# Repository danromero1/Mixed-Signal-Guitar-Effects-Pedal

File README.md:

# Mixed-Signal Guitar Effects Pedal

A standalone programmable guitar effects pedal implemented on a custom mixed-signal embedded platform with real-time DSP processing on an STM32 microcontroller.

---

## Overview

This project is the end-to-end design and bring-up of a custom 4-layer mixed-signal embedded platform for real-time audio acquisition, digital signal processing, and playback. An external high-resolution ADC and DAC interface with an STM32 microcontroller to enable deterministic, low-latency audio processing in a standalone system operating without a host PC.

The analog front end provides a high-impedance guitar input stage, precision biasing, and a 3rd-order Butterworth anti-aliasing filter to condition signals prior to conversion. Reconstruction filtering and low-noise output buffering suppress imaging artifacts and maintain low distortion across the audible band. PCB layout emphasizes controlled return paths, analog–digital domain isolation, low-impedance grounding, and consistent impedance to minimize coupling between sensitive analog circuitry and high-speed digital switching.

Power delivery is implemented using a USB-C input feeding a multi-rail regulation architecture to support low-noise analog supplies and regulated digital rails. All power stages and filter networks were simulated and validated in LTspice prior to layout. Decoupling and bypass networks were optimized per device requirements to ensure supply stability under dynamic load conditions.

Firmware is developed bare-metal in STM32CubeIDE using timer-triggered ADC sampling, DMA-based double buffering, and deterministic interrupt scheduling. Digital signal processing algorithms—including soft-clipping distortion, equalization, and filtering—are implemented in C using the CMSIS-DSP library on a Cortex-M4 FPU platform. The system targets a 48 kHz sample rate with sub-5 ms end-to-end latency to preserve instrument responsiveness.

The platform serves as a practical environment for developing embedded firmware architecture, hardware–software co-design techniques, signal integrity practices, and real-time performance analysis while producing a functional guitar effects processor from schematic to working prototype.

---

## Key Objectives

- Design and validate a professional-grade mixed-signal PCB for low-noise audio applications  
- Implement deterministic real-time audio processing on embedded hardware  
- Develop practical experience with ADC/DAC interfacing, buffering, and latency management  
- Integrate hardware bring-up, firmware development, and signal characterization into a complete system  

---

## Features

### Hardware
- STM32 microcontroller with floating-point acceleration  
- External high-resolution ADC and DAC for audio conversion  
- 4-layer PCB optimized for signal integrity and power integrity  
- 3rd-order Butterworth analog anti-aliasing filter  
- USB-C powered multi-rail regulation architecture  

### DSP
- Bare-metal real-time audio pipeline  
- DMA-based double buffering  
- Soft-clipping distortion processing  
- Digital equalization and filtering  
- Deterministic sampling and low-latency operation  

---

## Technical Stack

### Hardware
- STM32 Microcontroller (ARM Cortex-M4 with FPU)  
- External high-resolution ADC and DAC  
- 4-layer PCB with controlled impedance and solid reference planes  
- USB-C power delivery and multi-rail regulation  

### Software & Tools
- KiCad – Schematic capture and PCB layout  
- STM32CubeIDE – Bare-metal firmware development  
- CMSIS-DSP – Optimized DSP library  
- LTspice – Circuit simulation and filter verification  
- C/C++ – Embedded firmware implementation  

---

## Design Process

### Circuit Design & Simulation
Analog input and output stages were designed for guitar signal conditioning, biasing, and bandwidth control. A 3rd-order Butterworth anti-aliasing filter was simulated and verified in LTspice along with ADC/DAC interfacing and power regulation networks.

### PCB Layout (4-Layer Stack-Up)

- **Layer 1:** Top signal layer (components, sensitive analog routing, high-speed digital signals)  
- **Layer 2:** Solid ground plane for low-impedance return paths and noise control  
- **Layer 3:** Secondary reference plane for shielding and analog/digital isolation  
- **Layer 4:** Bottom signal layer for routing and power distribution  

**Design considerations include:**
- Analog and digital domain isolation  
- Controlled impedance routing for high-speed signals  
- Low-inductance return paths and continuous reference planes  
- Robust decoupling and power integrity practices  

### Firmware Architecture

Firmware configures ADC, DAC, timers, DMA, and interrupt scheduling to form a deterministic real-time audio pipeline. Audio samples are acquired using timer-triggered ADC conversions, buffered via DMA, processed in interrupt callbacks, and streamed to the DAC with minimal jitter and latency.

DSP algorithms are implemented in C using CMSIS-DSP primitives and floating-point arithmetic to accelerate development and maintain numerical stability.

---

## Development Status

### Completed
- Schematic design and circuit simulation  
- 3rd-order Butterworth filter design and verification  
- 4-layer PCB layout and stack-up definition  
- Component selection and BOM creation  

### In Progress
- Bare-metal firmware development  
- Real-time DSP implementation  
- PCB fabrication and assembly  

### Planned
- Hardware bring-up and validation  
- Audio performance measurement and characterization  
- Enclosure design and mechanical integration  
- Additional DSP effects (chorus, delay, reverb)  

---

## Technical Specifications

### Audio Path
- Input Impedance: 1 MΩ  
- Sample Rate: 48 kHz  
- Bit Depth: 16–24 bit (ADC dependent)  
- Frequency Response: 20 Hz – 20 kHz  
- Anti-Aliasing Filter: 3rd-order Butterworth, fc ≈ 20 kHz  

### Power
- Input: USB-C (5 V)  
- Internal Rails: 3.3 V (digital), ±5 V or +9 V (analog)  
- Estimated Current Consumption: 200–300 mA  

### Processing
- MCU: STM32 ARM Cortex-M4 with FPU  
- Target End-to-End Latency: < 5 ms  

---

## Engineering Focus

This project provides hands-on experience in:

- Mixed-signal PCB design and layout techniques  
- Real-time embedded firmware development  
- DMA-based buffering and interrupt-driven architectures  
- Analog signal conditioning and filter design  
- Audio signal processing fundamentals  
- Hardware bring-up and debugging on custom PCBs  
- Hardware–software co-design tradeoffs  

---

## Roadmap

### Phase 1 — Core Development (Current)
- Complete DSP firmware implementation  
- Fabricate and assemble PCB  
- Initial bring-up and debugging  

### Phase 2 — Refinement
- Audio performance characterization  
- Latency and CPU utilization optimization  
- PCB revision based on test results  

### Phase 3 — Enhancement
- Additional DSP effects  
- USB parameter control interface  
- Enclosure design and fabrication  

---

## References

### DSP
- *The Scientist and Engineer's Guide to Digital Signal Processing* — Steven W. Smith  
- *Understanding Digital Signal Processing* — Richard G. Lyons  
- *Small Signal Audio Design* — Douglas Self  

### Application Notes
- STM32 Audio Processing Application Notes  
- High-Speed PCB Design Guidelines  
- Audio ADC/DAC Interface Best Practices  

---

## License

This project is licensed under the MIT License. See the [LICENSE](LICENSE) file for details.

---

## Contact

**Daniel Romero**  
Email: daniel.romero@ieee.org  
Portfolio: https://electricalromero.com  
LinkedIn: https://www.linkedin.com/in/daniel-romero-ee/  

---

_Last updated: January 2026_

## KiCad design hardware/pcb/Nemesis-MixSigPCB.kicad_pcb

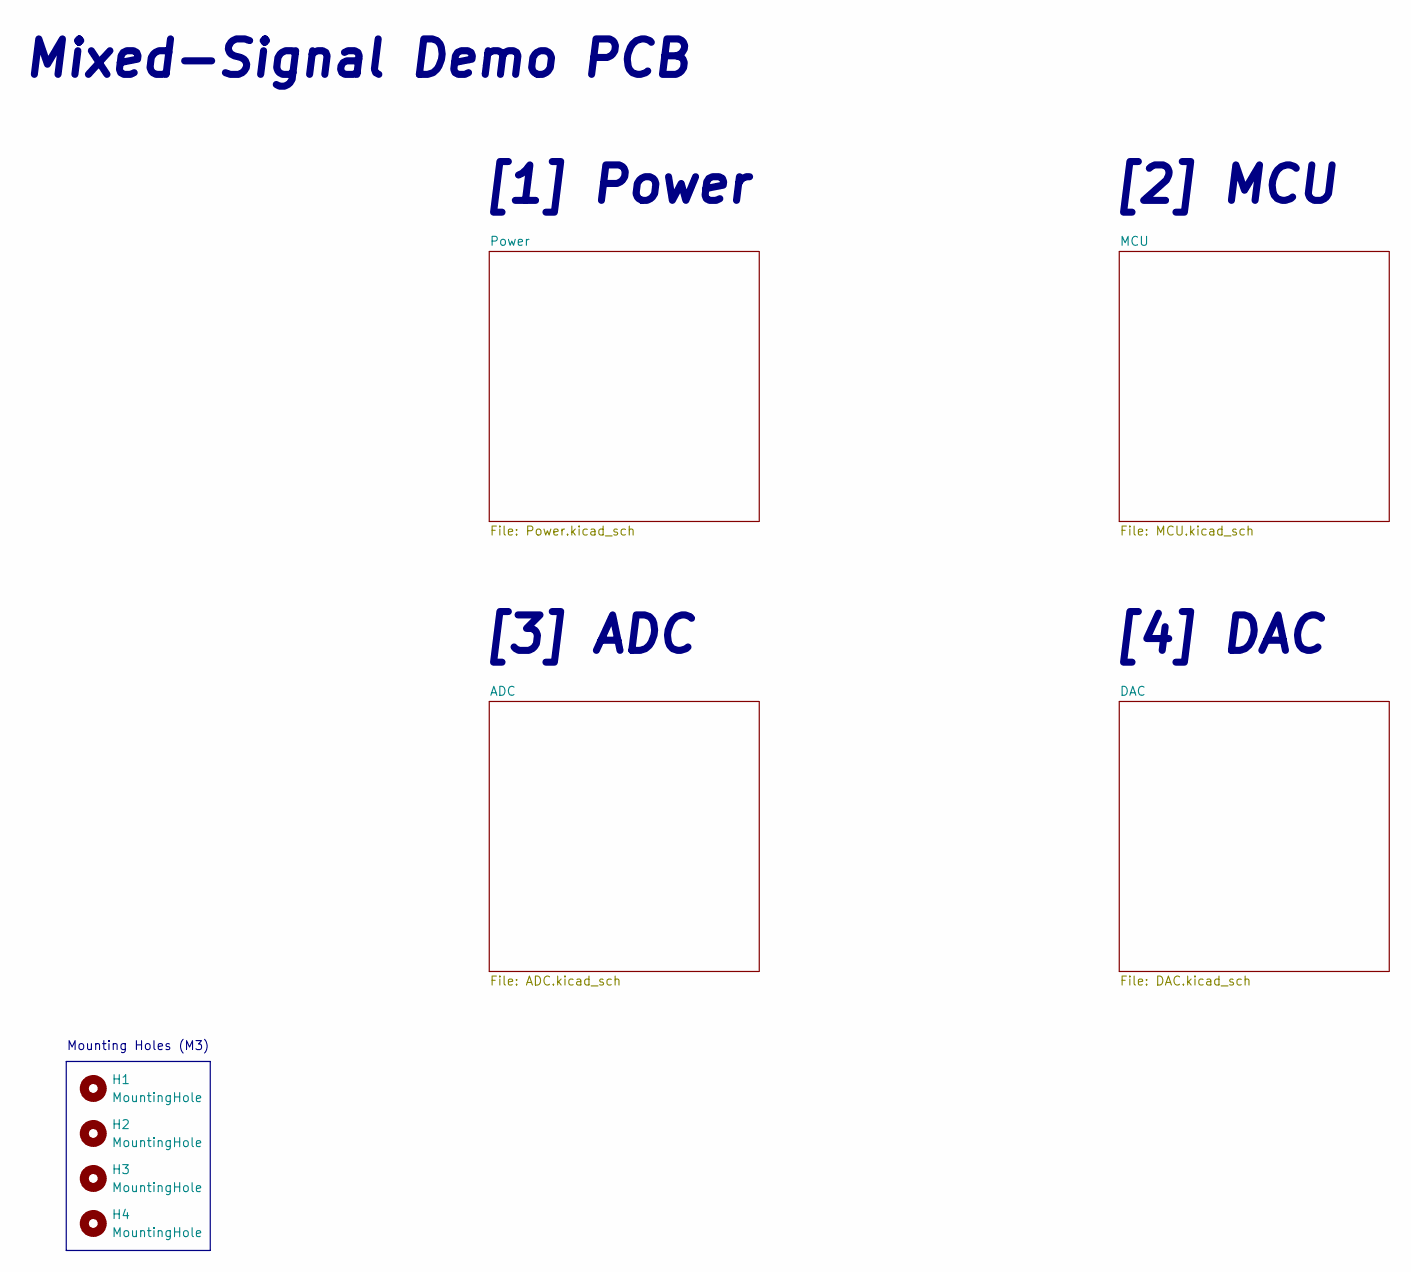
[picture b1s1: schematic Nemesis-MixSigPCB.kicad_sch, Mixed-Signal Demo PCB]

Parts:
H1, H2, H3, H4: MountingHole; MountingHole_3.2mm_M3

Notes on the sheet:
[4] DAC
Mixed-Signal Demo PCB
[3] ADC
Mounting Holes (M3)
[2] MCU
[1] Power

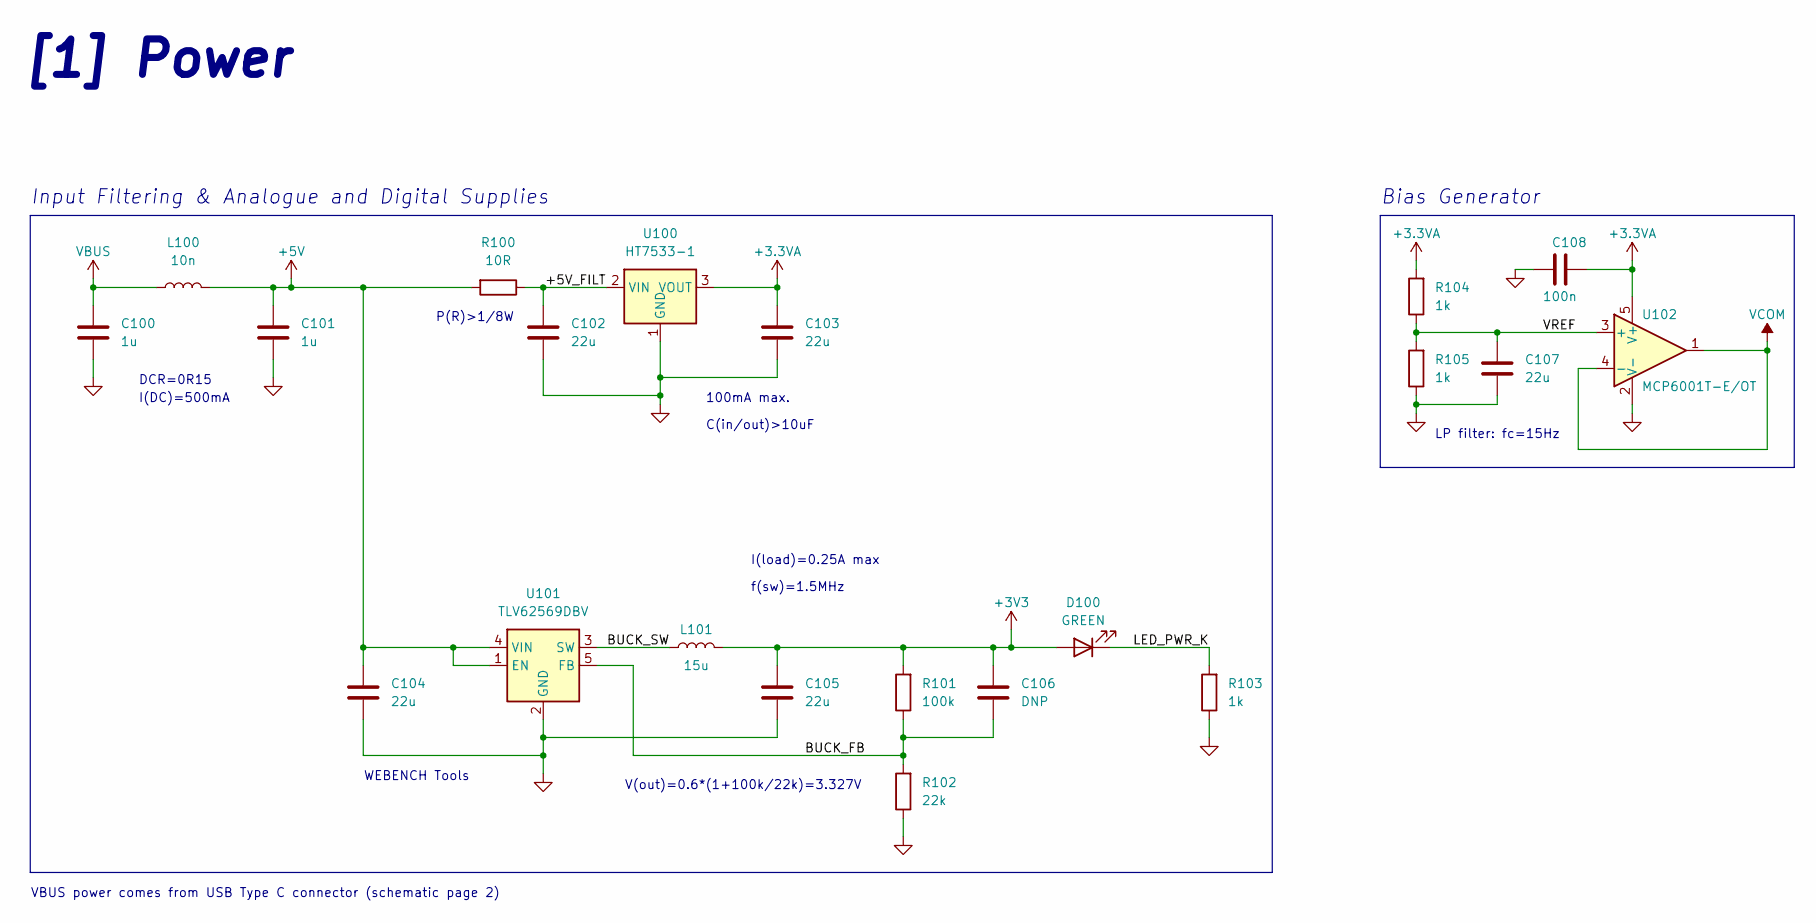
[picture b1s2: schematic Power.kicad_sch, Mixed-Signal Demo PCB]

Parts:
C100, C101: 1u; C_0603_1608Metric; Manufacturer Part Number CL10A105KB8NNNC
C102, C103, C104, C105, C107: 22u; C_0805_2012Metric; Manufacturer Part Number CL21A226MAQNNNE
C106: DNP; C_0402_1005Metric
C108: 100n; C_0402_1005Metric; Manufacturer Part Number CL05B104KO5NNNC
D100: GREEN; LED_0603_1608Metric; Manufacturer Part Number 19-217/GHC-YR1S2/3T
L100: 10n; L_0402_1005Metric; Manufacturer Part Number SDCL1005C10NJTDF
L101: 15u; L_Sunlord_MWSA0603S; Manufacturer Part Number MWSA0603S-150MT
R100: 10R; R_0805_2012Metric; Manufacturer Part Number 0805W8F100JT5E
R101: 100k; R_0402_1005Metric; Manufacturer Part Number 0402WGF1003TCE
R102: 22k; R_0402_1005Metric; Manufacturer Part Number 0402WGF2202TCE
R103, R104, R105: 1k; R_0402_1005Metric; Manufacturer Part Number 0402WGF1001TCE
U100: HT7533-1; SOT-89-3; Manufacturer Part Number HT7533-1
U101: TLV62569DBV; SOT-23-5; Manufacturer Part Number TLV62569DBVR
U102: MCP6001T-E/OT; SOT-23-5; Manufacturer Part Number MCP6001T-E/OT

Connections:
+3.3VA: C103.1, C108.1, R104.2, U100.3 (VOUT), U102.5 (V+); also elsewhere on the board
+3V3: C105.1, C106.1, D100.2 (A), L101.2, R101.2; also elsewhere on the board
+5V: C101.1, C104.1, L100.2, R100.2, U101.1 (EN), U101.4 (VIN); also elsewhere on the board
/Power/+5V_FILT: C102.1, R100.1, U100.2 (VIN)
/Power/BUCK_FB: C106.2, R101.1, R102.2, U101.5 (FB)
/Power/BUCK_SW: L101.1, U101.3 (SW)
/Power/LED_PWR_K: D100.1 (K), R103.2
/Power/VREF: C107.1, R104.1, R105.2, U102.3 (+)
GND: C100.2, C101.2, C102.2, C103.2, C104.2, C105.2, C107.2, C108.2, R102.1, R103.1, R105.1, U100.1 (GND), U101.2 (GND), U102.2 (V-); also elsewhere on the board
VBUS: C100.1, L100.1; also elsewhere on the board
VCOM: U102.1, U102.4 (-); also elsewhere on the board

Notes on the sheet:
DCR=0R15
C(in/out)>10uF
V(out)=0.6*(1+100k/22k)=3.327V
I(DC)=500mA
Bias Generator
LP filter: fc=15Hz
100mA max.
f(sw)=1.5MHz
VBUS power comes from USB Type C connector (schematic page 2)
P(R)>1/8W
I(load)=0.25A max
Input Filtering & Analogue and Digital Supplies
[1] Power
WEBENCH Tools

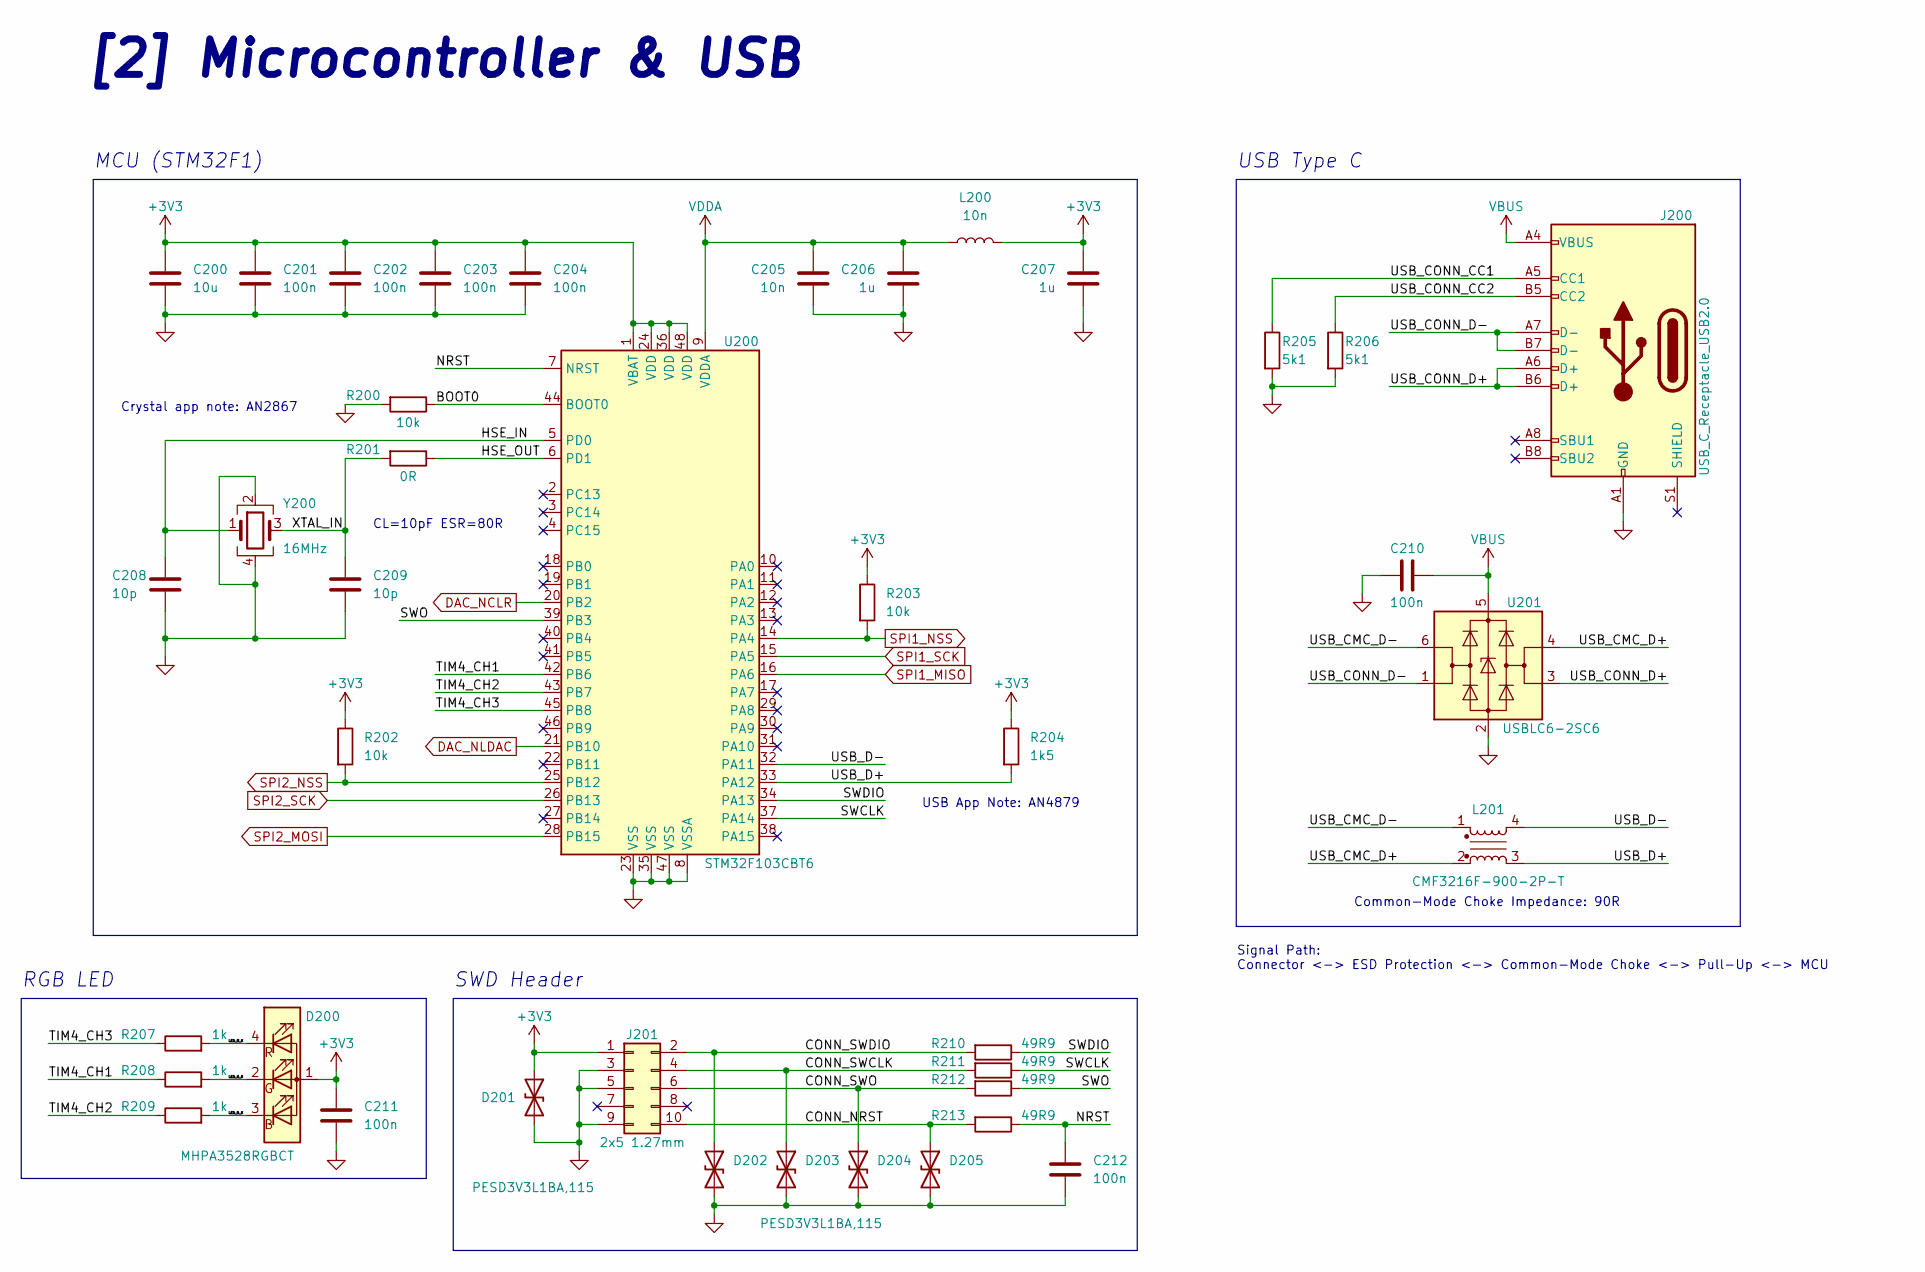
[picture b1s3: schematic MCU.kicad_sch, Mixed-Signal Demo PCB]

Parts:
C200: 10u; C_0603_1608Metric; Manufacturer Part Number CL10A106MA8NRNC
C201, C202, C203, C204, C210, C211, C212: 100n; C_0402_1005Metric; Manufacturer Part Number CL05B104KO5NNNC
C205: 10n; C_0402_1005Metric; Manufacturer Part Number CL05B103KB5NNNC
C206, C207: 1u; C_0603_1608Metric; Manufacturer Part Number CL10A105KB8NNNC
C208, C209: 10p; C_0402_1005Metric; Manufacturer Part Number CL05C100JB5NNNC
D200: MHPA3528RGBCT; Manufacturer Part Number MHPA3528RGBCT
D201, D202, D203, D204, D205: PESD3V3L1BA,115; D_SOD-323; Manufacturer Part Number PESD3V3L1BA,115
J200: USB_C_Receptacle_USB2.0; USB_C_Receptacle_HRO_TYPE-C-31-M-12; Manufacturer Part Number TYPE-C-31-M-12
J201: 2x5 1.27mm; PinHeader_2x05_P1.27mm_Vertical_SMD; Manufacturer Part Number FTSH-105-01-F-DV-K-TR
L200: 10n; L_0402_1005Metric; Manufacturer Part Number SDCL1005C10NJTDF
L201: CMF3216F-900-2P-T; L_CommonModeChoke_CMF3216F-900-2P-T; Manufacturer Part Number CMF3216F-900-2P-T
R200, R202, R203: 10k; R_0402_1005Metric; Manufacturer Part Number 0402WGF1002TCE
R201: 0R; R_0402_1005Metric; Manufacturer Part Number 0402WGF0000TCE
R204: 1k5; R_0402_1005Metric; Manufacturer Part Number 0402WGF1501TCE
R205, R206: 5k1; R_0402_1005Metric; Manufacturer Part Number 0402WGF5101TCE
R207, R208, R209: 1k; R_0402_1005Metric; Manufacturer Part Number 0402WGF1001TCE
R210, R211, R212, R213: 49R9; R_0402_1005Metric; Manufacturer Part Number 0402WGF499JTCE
U200: STM32F103CBT6; LQFP-48_7x7mm_P0.5mm; Manufacturer Part Number STM32F103CBT6
U201: USBLC6-2SC6; SOT-23-6; Manufacturer Part Number USBLC6-2SC6
Y200: 16MHz; Crystal_SMD_3225-4Pin_3.2x2.5mm; Manufacturer Part Number 7M16000017

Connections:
+3V3: C200.1, C201.1, C202.1, C203.1, C204.1, C207.1, C211.1, D200.1 (A), D201.1 (A1), J201.1 (Vcc), L200.2, R202.1, R203.1, R204.1, U200.1 (VBAT), U200.24 (VDD), U200.36 (VDD), U200.48 (VDD); also elsewhere on the board
/MCU/BOOT0: R200.1, U200.44 (BOOT0)
/MCU/CONN_NRST: D205.1 (A1), J201.10 (NRST), R213.2
/MCU/CONN_SWCLK: D203.1 (A1), J201.4 (SWDCLK), R211.2
/MCU/CONN_SWDIO: D202.1 (A1), J201.2 (SWDIO), R210.2
/MCU/CONN_SWO: D204.1 (A1), J201.6 (SWO), R212.2
/MCU/HSE_IN: C208.1, U200.5 (PD0), Y200.1
/MCU/HSE_OUT: R201.1, U200.6 (PD1)
/MCU/LED_B_K: D200.3 (BK), R209.2
/MCU/LED_G_K: D200.2 (GK), R208.2
/MCU/LED_R_K: D200.4 (RK), R207.2
/MCU/NRST: C212.1, R213.1, U200.7 (NRST)
/MCU/SWCLK: R211.1, U200.37 (PA14)
/MCU/SWDIO: R210.1, U200.34 (PA13)
/MCU/SWO: R212.1, U200.39 (PB3)
/MCU/TIM4_CH1: R208.1, U200.42 (PB6)
/MCU/TIM4_CH2: R209.1, U200.43 (PB7)
/MCU/TIM4_CH3: R207.1, U200.45 (PB8)
/MCU/USB_CMC_D+: L201.2, U201.4 (I/O2)
/MCU/USB_CMC_D-: L201.1, U201.6 (I/O1)
/MCU/USB_CONN_CC1: J200.A5 (CC1), R205.1
/MCU/USB_CONN_CC2: J200.B5 (CC2), R206.1
/MCU/USB_CONN_D+: J200.A6 (D+), J200.B6 (D+), U201.3 (I/O2)
/MCU/USB_CONN_D-: J200.A7 (D-), J200.B7 (D-), U201.1 (I/O1)
/MCU/USB_D+: L201.3, R204.2, U200.33 (PA12)
/MCU/USB_D-: L201.4, U200.32 (PA11)
/MCU/XTAL_IN: C209.1, R201.2, Y200.3
DAC_NCLR: U200.20 (PB2); also elsewhere on the board
DAC_NLDAC: U200.21 (PB10); also elsewhere on the board
GND: C200.2, C201.2, C202.2, C203.2, C204.2, C205.2, C206.2, C207.2, C208.2, C209.2, C210.2, C211.2, C212.2, D201.2 (A2), D202.2 (A2), D203.2 (A2), D204.2 (A2), D205.2 (A2), J200.A1 (GND), J200.A12 (GND), J200.B1 (GND), J200.B12 (GND), J201.3 (GND), J201.5 (GND), J201.9 (GNDDetect), R200.2, R205.2, R206.2, U200.8 (VSSA), U200.23 (VSS), U200.35 (VSS), U200.47 (VSS), U201.2 (GND), Y200.2, Y200.4; also elsewhere on the board
SPI1_MISO: U200.16 (PA6); also elsewhere on the board
SPI1_NSS: R203.2, U200.14 (PA4); also elsewhere on the board
SPI1_SCK: U200.15 (PA5); also elsewhere on the board
SPI2_MOSI: U200.28 (PB15); also elsewhere on the board
SPI2_NSS: R202.2, U200.25 (PB12); also elsewhere on the board
SPI2_SCK: U200.26 (PB13); also elsewhere on the board
VBUS: C210.1, J200.A4 (VBUS), J200.A9 (VBUS), J200.B4 (VBUS), J200.B9 (VBUS), U201.5 (VBUS); also elsewhere on the board
VDDA: C205.1, C206.1, L200.1, U200.9 (VDDA)

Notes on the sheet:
Signal Path: Connector <-> ESD Protection <-> Common-Mode Choke <-> Pull-Up <-> MCU
RGB LED
Crystal app note: AN2867
SWD Header
USB App Note: AN4879
Common-Mode Choke Impedance: 90R
[2] Microcontroller & USB
CL=10pF ESR=80R
MCU (STM32F1)
USB Type C

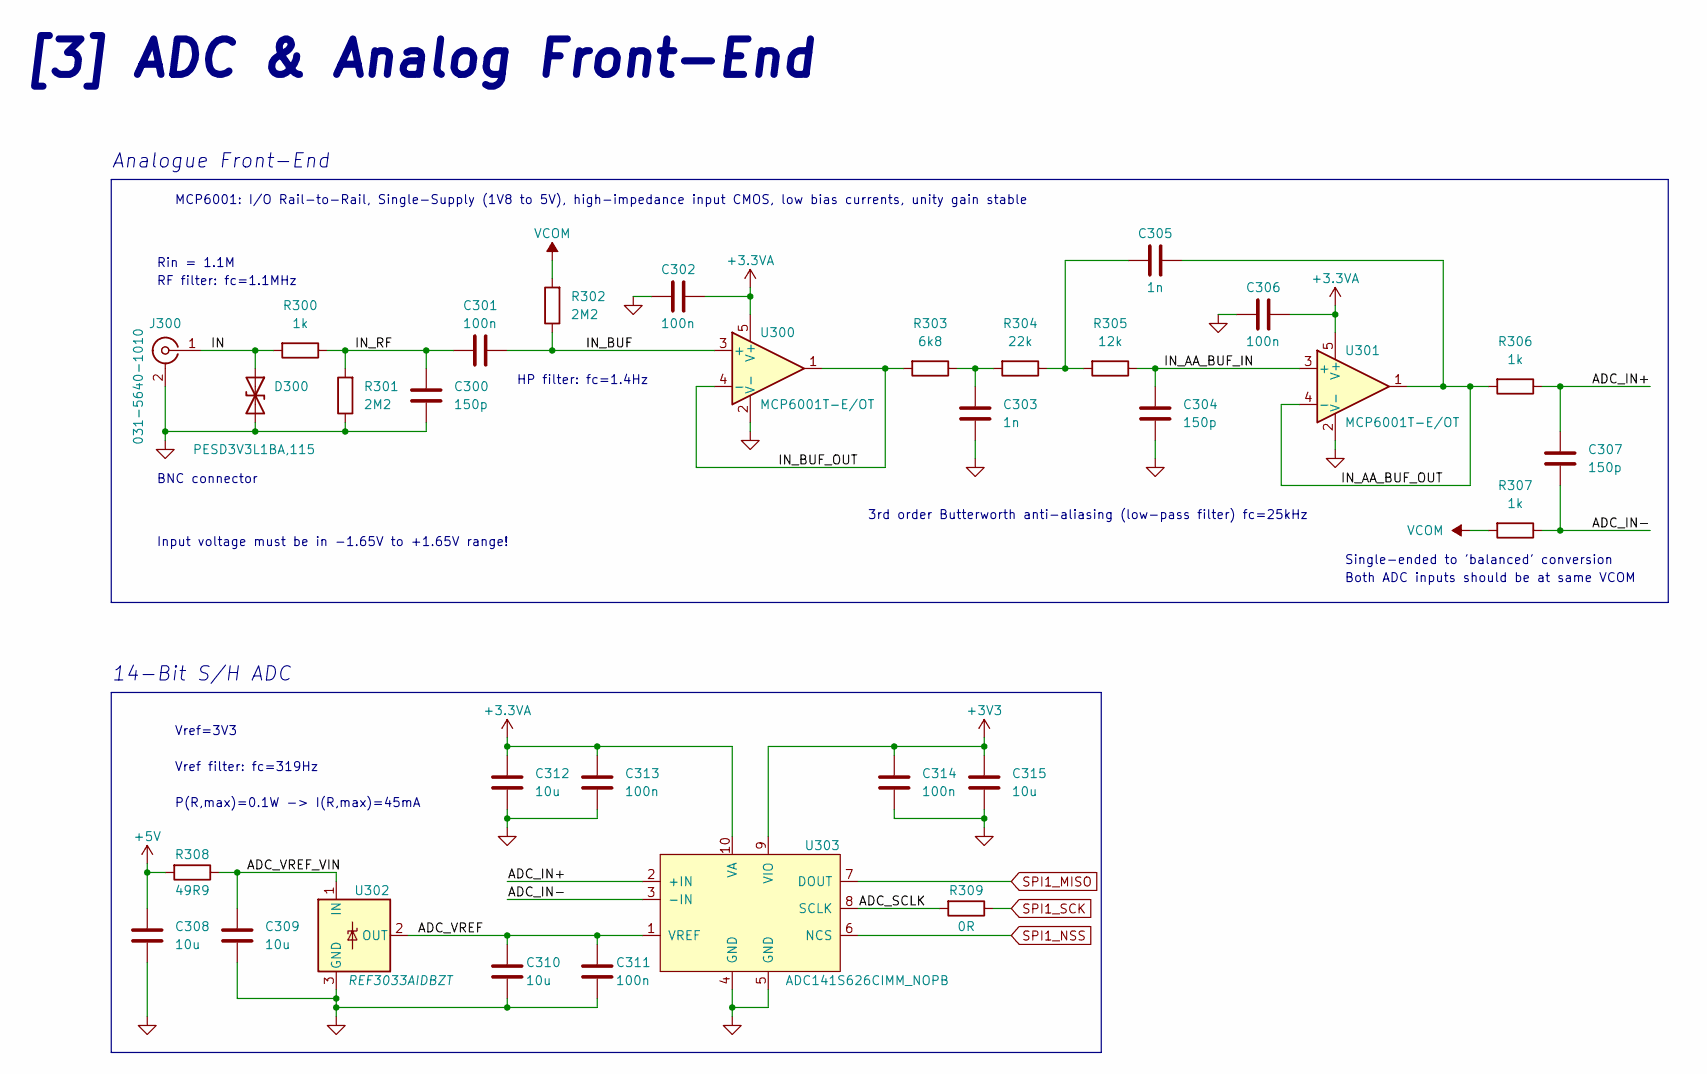
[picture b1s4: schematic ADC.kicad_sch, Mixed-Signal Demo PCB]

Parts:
C300, C304, C307: 150p; C_0402_1005Metric; Manufacturer Part Number CL05C151JB5NNNC
C301, C302, C306, C311, C313, C314: 100n; C_0402_1005Metric; Manufacturer Part Number CL05B104KO5NNNC
C303, C305: 1n; C_0402_1005Metric; Manufacturer Part Number 0402B102K500NT
C308, C309, C310, C312, C315: 10u; C_0603_1608Metric; Manufacturer Part Number CL10A106MA8NRNC
D300: PESD3V3L1BA,115; D_SOD-323; Manufacturer Part Number PESD3V3L1BA,115
J300: 031-5640-1010; AMPHENOL-BNC-031-5640-1010; Manufacturer Part Number 031-5640
R300, R306, R307: 1k; R_0402_1005Metric; Manufacturer Part Number 0402WGF1001TCE
R301, R302: 2M2; R_0402_1005Metric; Manufacturer Part Number 0402WGF2204TCE
R303: 6k8; R_0402_1005Metric; Manufacturer Part Number 0402WGF6801TCE
R304: 22k; R_0402_1005Metric; Manufacturer Part Number 0402WGF2202TCE
R305: 12k; R_0402_1005Metric; Manufacturer Part Number 0402WGF1202TCE
R308: 49R9; R_0402_1005Metric; Manufacturer Part Number 0402WGF499JTCE
R309: 0R; R_0402_1005Metric; Manufacturer Part Number 0402WGF0000TCE
U300, U301: MCP6001T-E/OT; SOT-23-5; Manufacturer Part Number MCP6001T-E/OT
U302: REF3033AIDBZT; SOT-23; Manufacturer Part Number REF3033AIDBZT
U303: ADC141S626CIMM_NOPB; VSSOP-10_3x3mm_P0.5mm; Manufacturer Part Number ADC141S626CIMM/NOPB

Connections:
+3.3VA: C302.1, C306.1, C312.1, C313.1, U300.5 (V+), U301.5 (V+), U303.10 (VA); also elsewhere on the board
+3V3: C314.1, C315.1, U303.9 (VIO); also elsewhere on the board
+5V: C308.1, R308.2; also elsewhere on the board
/ADC/ADC_IN+: C307.1, R306.1, U303.2 (+IN)
/ADC/ADC_IN-: C307.2, R307.1, U303.3 (-IN)
/ADC/ADC_SCLK: R309.2, U303.8 (SCLK)
/ADC/ADC_VREF: C310.1, C311.1, U302.2 (OUT), U303.1 (VREF)
/ADC/ADC_VREF_VIN: C309.1, R308.1, U302.1 (IN)
/ADC/IN: D300.1 (A1), J300.1 (In), R300.2
/ADC/IN_AA_BUF_IN: C304.1, R305.1, U301.3 (+)
/ADC/IN_AA_BUF_OUT: C305.2, R306.2, U301.1, U301.4 (-)
/ADC/IN_BUF: C301.1, R302.1, U300.3 (+)
/ADC/IN_BUF_OUT: R303.2, U300.1, U300.4 (-)
/ADC/IN_RF: C300.1, C301.2, R300.1, R301.2
GND: C300.2, C302.2, C303.2, C304.2, C306.2, C308.2, C309.2, C310.2, C311.2, C312.2, C313.2, C314.2, C315.2, D300.2 (A2), J300.2 (Ext), R301.1, U300.2 (V-), U301.2 (V-), U302.3 (GND), U303.4 (GND), U303.5 (GND); also elsewhere on the board
unnamed: C303.1, R303.1, R304.2
unnamed: C305.1, R304.1, R305.2
SPI1_MISO: U303.7 (DOUT); also elsewhere on the board
SPI1_NSS: U303.6 (NCS); also elsewhere on the board
SPI1_SCK: R309.1; also elsewhere on the board
VCOM: R302.2, R307.2; also elsewhere on the board

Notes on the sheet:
HP filter: fc=1.4Hz
Both ADC inputs should be at same VCOM
BNC connector
Rin = 1.1M
14-Bit S/H ADC
Vref filter: fc=319Hz
Input voltage must be in -1.65V to +1.65V range!
Analogue Front-End
Single-ended to 'balanced' conversion
RF filter: fc=1.1MHz
3rd order Butterworth anti-aliasing (low-pass filter) fc=25kHz
MCP6001: I/O Rail-to-Rail, Single-Supply (1V8 to 5V), high-impedance input CMOS, low bias currents, unity gain stable
P(R,max)=0.1W -> I(R,max)=45mA
Vref=3V3
[3] ADC & Analog Front-End

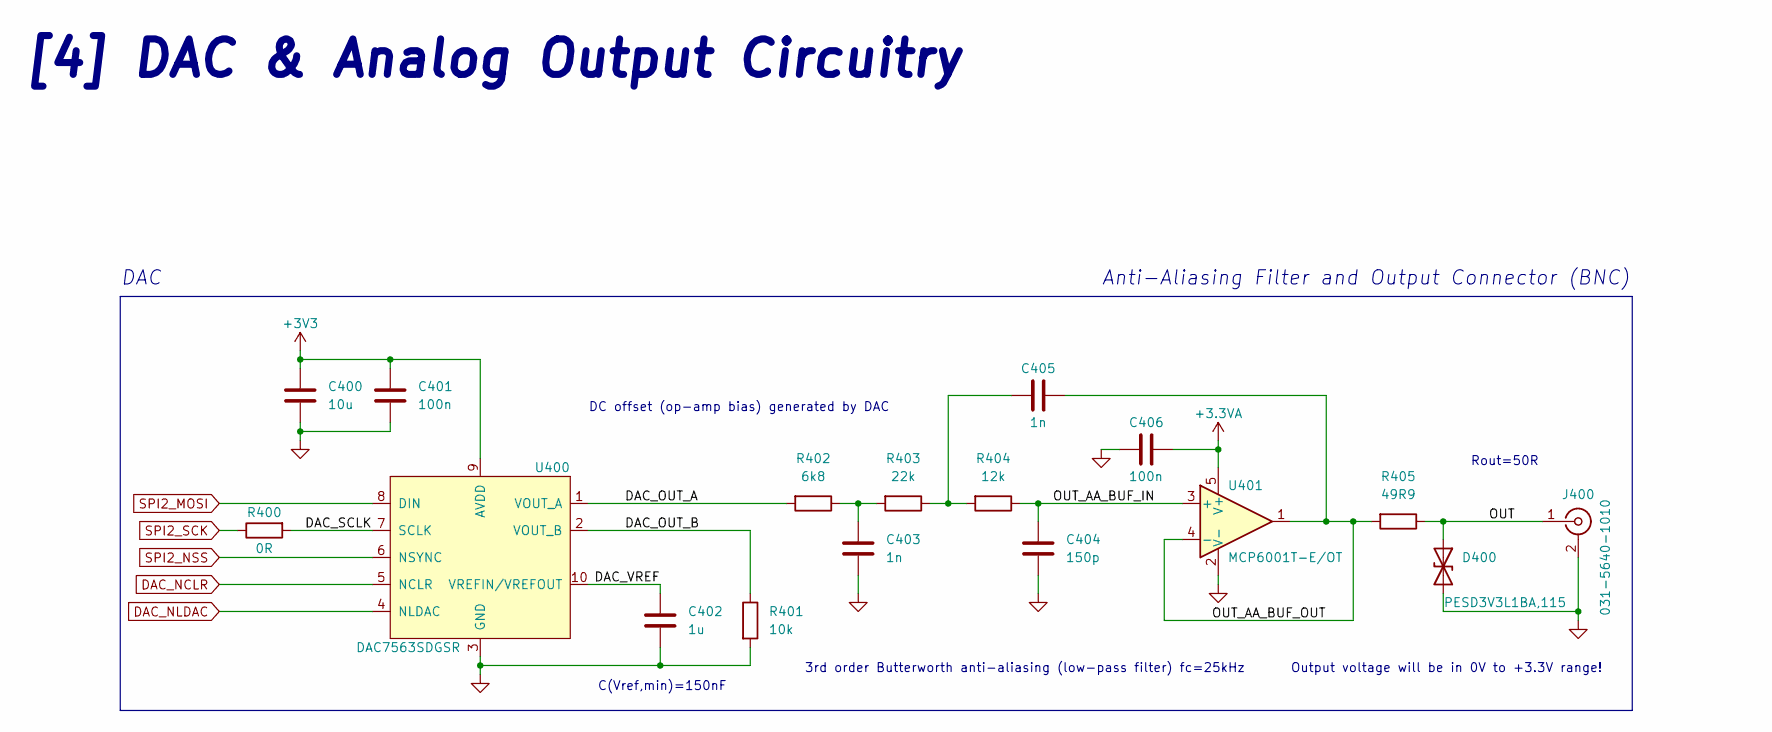
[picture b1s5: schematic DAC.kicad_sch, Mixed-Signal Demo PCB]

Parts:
C400: 10u; C_0603_1608Metric; Manufacturer Part Number CL10A106MA8NRNC
C401, C406: 100n; C_0402_1005Metric; Manufacturer Part Number CL05B104KO5NNNC
C402: 1u; C_0603_1608Metric; Manufacturer Part Number CL10A105KB8NNNC
C403, C405: 1n; C_0402_1005Metric; Manufacturer Part Number 0402B102K500NT
C404: 150p; C_0402_1005Metric; Manufacturer Part Number CL05C151JB5NNNC
D400: PESD3V3L1BA,115; D_SOD-323; Manufacturer Part Number PESD3V3L1BA,115
J400: 031-5640-1010; AMPHENOL-BNC-031-5640-1010; Manufacturer Part Number 031-5640
R400: 0R; R_0402_1005Metric; Manufacturer Part Number 0402WGF0000TCE
R401: 10k; R_0402_1005Metric; Manufacturer Part Number 0402WGF1002TCE
R402: 6k8; R_0402_1005Metric; Manufacturer Part Number 0402WGF6801TCE
R403: 22k; R_0402_1005Metric; Manufacturer Part Number 0402WGF2202TCE
R404: 12k; R_0402_1005Metric; Manufacturer Part Number 0402WGF1202TCE
R405: 49R9; R_0402_1005Metric; Manufacturer Part Number 0402WGF499JTCE
U400: DAC7563SDGSR; VSSOP-10_3x3mm_P0.5mm; Manufacturer Part Number DAC7563TDGSR
U401: MCP6001T-E/OT; SOT-23-5; Manufacturer Part Number MCP6001T-E/OT

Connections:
+3.3VA: C406.1, U401.5 (V+); also elsewhere on the board
+3V3: C400.1, C401.1, U400.9 (AVDD); also elsewhere on the board
/DAC/DAC_OUT_A: R402.2, U400.1 (VOUT_A)
/DAC/DAC_OUT_B: R401.1, U400.2 (VOUT_B)
/DAC/DAC_SCLK: R400.2, U400.7 (SCLK)
/DAC/DAC_VREF: C402.1, U400.10 (VREFIN/VREFOUT)
/DAC/OUT: D400.1 (A1), J400.1 (In), R405.1
/DAC/OUT_AA_BUF_IN: C404.1, R404.1, U401.3 (+)
/DAC/OUT_AA_BUF_OUT: C405.2, R405.2, U401.1, U401.4 (-)
DAC_NCLR: U400.5 (NCLR); also elsewhere on the board
DAC_NLDAC: U400.4 (NLDAC); also elsewhere on the board
GND: C400.2, C401.2, C402.2, C403.2, C404.2, C406.2, D400.2 (A2), J400.2 (Ext), R401.2, U400.3 (GND), U401.2 (V-); also elsewhere on the board
unnamed: C403.1, R402.1, R403.2
unnamed: C405.1, R403.1, R404.2
SPI2_MOSI: U400.8 (DIN); also elsewhere on the board
SPI2_NSS: U400.6 (NSYNC); also elsewhere on the board
SPI2_SCK: R400.1; also elsewhere on the board

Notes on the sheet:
[4] DAC & Analog Output Circuitry
Anti-Aliasing Filter and Output Connector (BNC)
Rout=50R
Output voltage will be in 0V to +3.3V range!
DAC
C(Vref,min)=150nF
3rd order Butterworth anti-aliasing (low-pass filter) fc=25kHz
DC offset (op-amp bias) generated by DAC

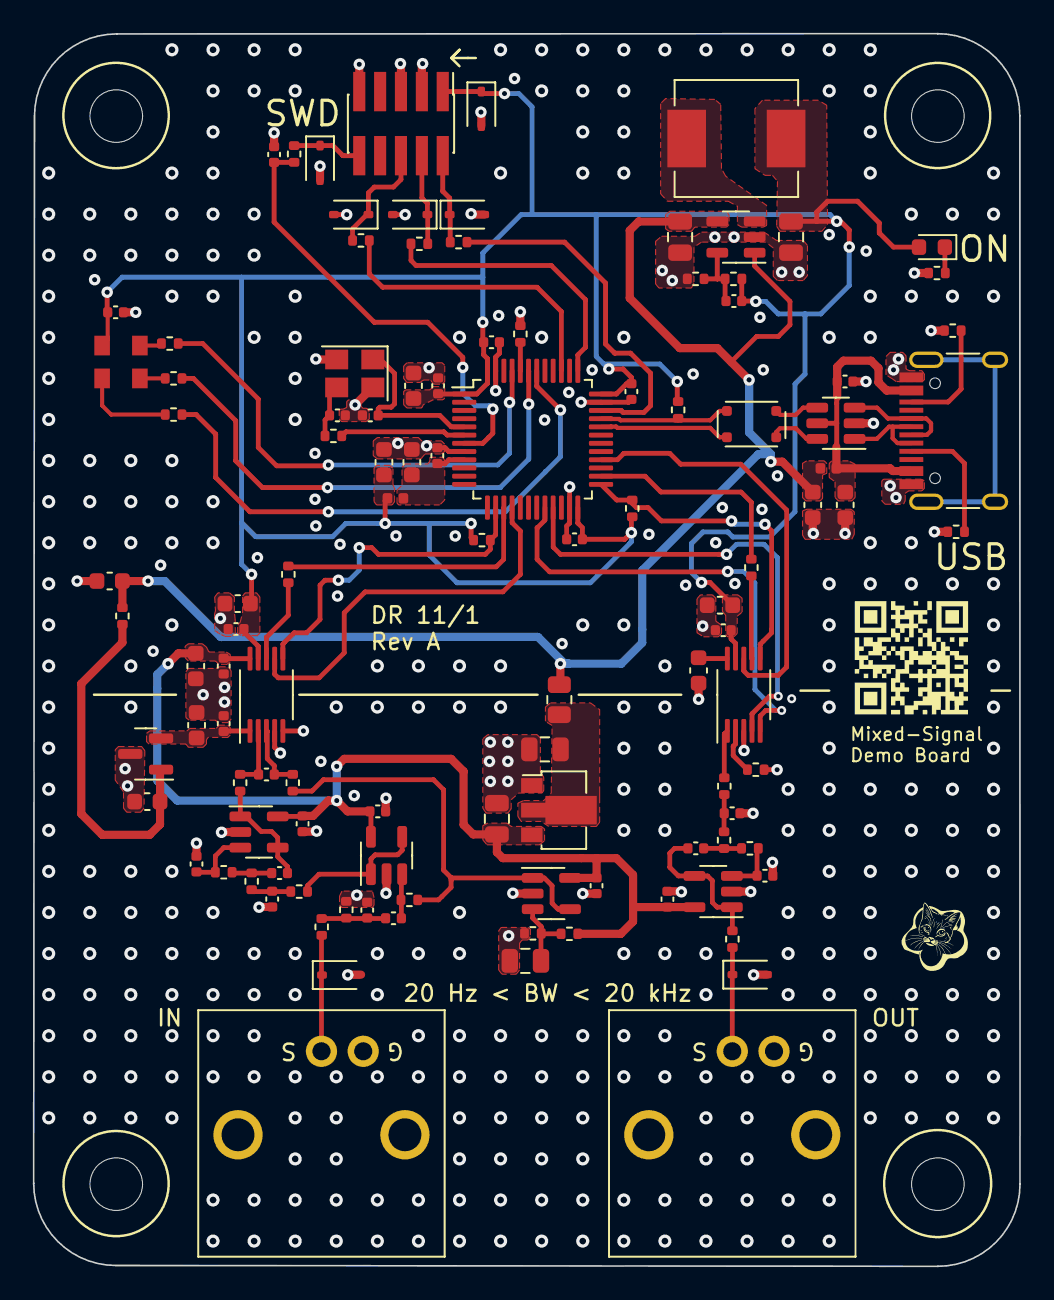
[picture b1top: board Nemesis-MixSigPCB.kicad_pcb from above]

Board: 4 copper layers, 60.0 x 75.0 mm, 114 parts (0 on the bottom side), 68 nets.

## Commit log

2026-01-03 Create schematics

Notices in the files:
README.md:
License: MIT
